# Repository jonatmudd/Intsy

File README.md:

# Intsy
32/64/128 channel bioamplifier system, now with accelerometer and on-board SD data logging capability for ambulatory applications! Photos of the original 32/64 channel device are below Also, check out the quick overview of the device internals and mechanical enclosure of the 128 channel ambulatory system in <a href =  "https://www.youtube.com/watch?v=RvYDtEdVOBU&feature=youtu.be">this video</a> (full credit to Riwaj Shrestha, Suyash Mathema, and Jeremy Wharton!).

Intsy is a validated, low-cost, open-source, wireless-enabled bioamplifier system.  The system can be configured for 32, 64, or 128 channel operation.  It has been validated for acquiring high-quality gastrointesinal slow wave and surface EMG electrical signals.  For more details, see our <a href =  "http://iopscience.iop.org/article/10.1088/1361-6579/aaad51">published peer-reviewed article in Physiological Measurement</a>. We have also regularly used Intsy to make <a href = "https://ieeexplore.ieee.org/abstract/document/8839813"> body surface recordings of colonic motilty patterns</a> using  conventiona wet (gel) as well as dry electrodes (see <a  href = "https://link.springer.com/article/10.1007/s10439-023-03137-w"> this journal article  </a>) 

Data can be streamed either in wired configuration over USB or wirelessly via bluetooth.  A LabView GUI allows for real-time visualization and saving to hard disk for off-line analysis.  Data rates of 32 chan x 110 Hz can be stably transmitted over bluetooth.  The USB wired configuration can achieve up to 2 kHz x 128 chan.  Matlab functions for converting binary Intsy data files into matlab format are provided.

The name Intsy comes from the two core components: Intan RHD2132 bioamplifier chip + Teensy 3.6 microcontroller.

Please see "Intsy_Setup_Guide.pdf" for detailed instructions on how to set up the 32/64 channel Intsy system. Assembly time is typically about 4 hrs.  Total cost is about $1500 for the 32 channel system,  $2400 for the 64 channel system, and $6000 for the 128 channel system (the dominant cost being the Intan RHD2132 amplifier boards).  That means  you can build your very own high-quality, low-cost, portable bioamplifier system in just a single afternoon!

All feedback and suggestions are warmly welcomed. 

Above: Intsy 128 channel electronics and mechanical enclosure (circa May 2020)

Above: Intsy hardware architecture and device (32/64 channel original module circa Dec 2017)

Above: Screenshot of Intsy Labview front end to visualize and stream signals in real time. The figure shows propagating gastric slow waves.

<p><font size="16"><b>Disclaimer</b></font></p>
The Intsy electronics module is not a medical device nor is it intended for medical diagnosis and provided to you "as is," and we make no express or implied warranties whatsoever with respect to its functionality, operability, or use, including, without limitation, any implied warranties, fitness for a particular purpose, or infringement. We expressly disclaim any liability whatsoever for any direct, indirect, consequential, incidental or special damages, including, without limitation, lost revenues, lost profits, losses resulting from business interruption or loss of data, regardless of the form of action or legal theory under which the liability may be asserted, even if advised of the possibility of such damages. This bioamplifier module does not fall within the scope of the European Union directives regarding electromagnetic compatibility, restricted substances (RoHS), recycling (WEEE), FCC, CE or UL, and therefore may not meet the technical requirements of these directives or other related directives

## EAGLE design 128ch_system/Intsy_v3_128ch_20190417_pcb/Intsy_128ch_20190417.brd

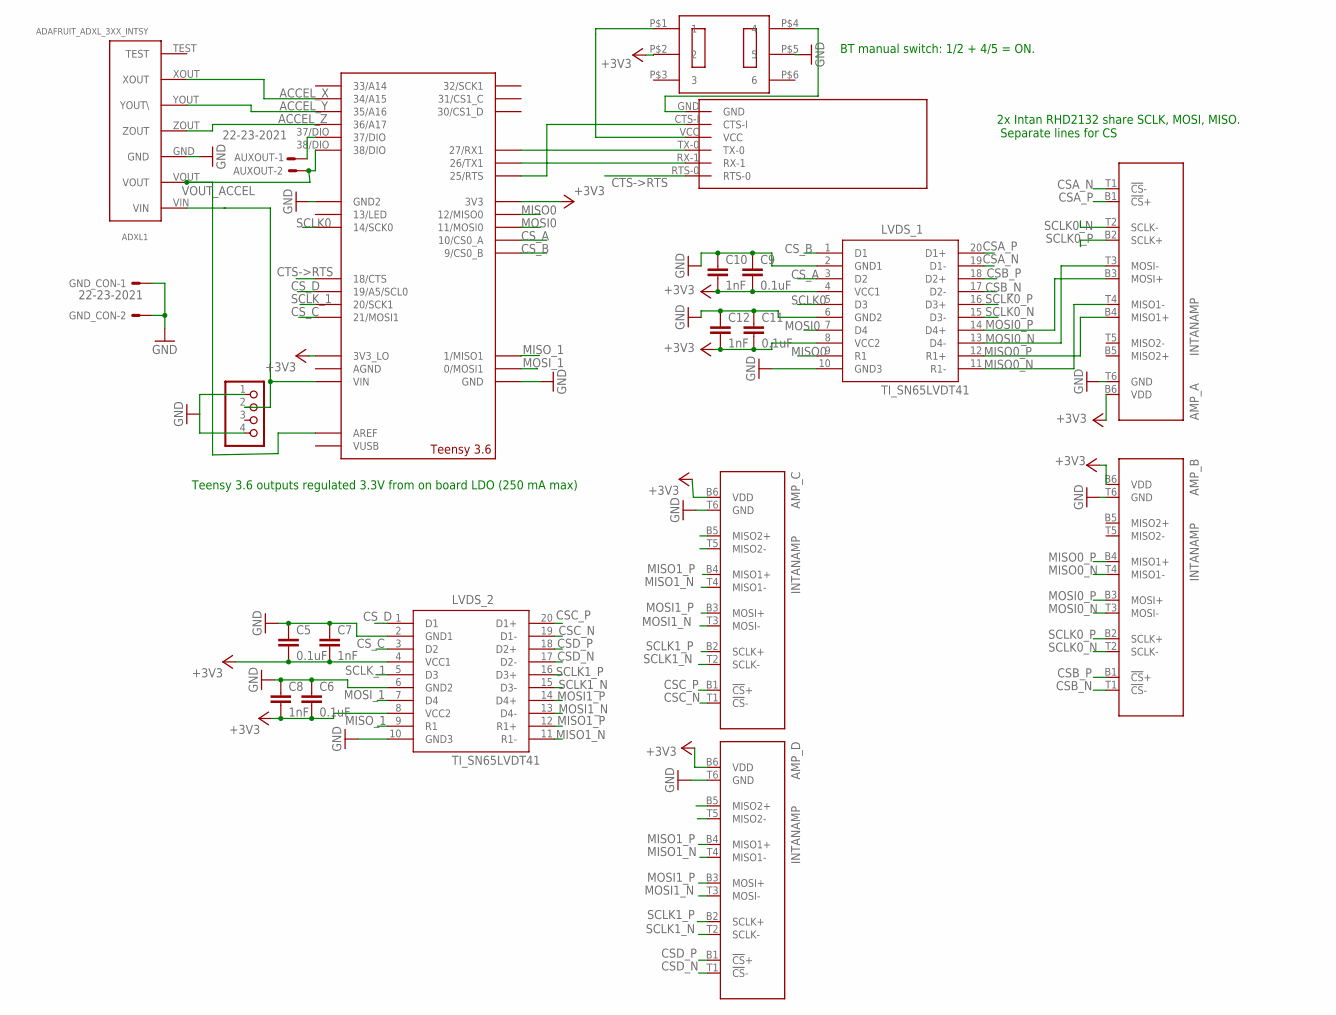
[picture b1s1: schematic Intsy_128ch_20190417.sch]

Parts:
ADXL1: ADAFRUIT_ADXL_3XX_INTSY; ADAFRUIT_ADXL_3XX
AMP_A: INTANAMP; AMPBOARD
AMP_B: INTANAMP; AMPBOARD
AMP_C: INTANAMP; AMPBOARD
AMP_D: INTANAMP; AMPBOARD
AUXOUT: 22-23-2021
C5, C6, C9, C11: 0.1uF; C2012
C7, C8, C10, C12: 1nF; C2012
DPDT_1: DPDT_1; SLIDE_SWITCH_DPDT_NIDEC
GND_CON: 22-23-2021
LVDS_1, LVDS_2: TI_SN65LVDT41; SN65LVDT41_TSSOP20
RN42: RN42
SW1: LiPoIn; PADS-4
U$2: TEENSY_3.5/3.6_SIMPLE

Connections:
+3V3: AMP_A.B6 (VDD), AMP_B.B6 (VDD), AMP_C.B6 (VDD), AMP_D.B6 (VDD), C5.2, C6.2, C7.2, C8.2, C9.2, C10.2, C11.2, C12.2, DPDT_1.P$2 (2), LVDS_1.4 (VCC1), LVDS_1.8 (VCC2), LVDS_2.4 (VCC1), LVDS_2.8 (VCC2), U$2.3V3, U$2.3V3_LO
ACCEL_X: ADXL1.XOUT, U$2.34/A15
ACCEL_Y: ADXL1.YOUT (YOUT\), U$2.35/A16
ACCEL_Z: ADXL1.ZOUT, U$2.36/A17
CSA_N: AMP_A.T1 (!CS!-), LVDS_1.19 (D1-)
CSA_P: AMP_A.B1 (!CS!+), LVDS_1.20 (D1+)
CSB_N: AMP_B.T1 (!CS!-), LVDS_1.17 (D2-)
CSB_P: AMP_B.B1 (!CS!+), LVDS_1.18 (D2+)
CSC_N: AMP_C.T1 (!CS!-), LVDS_2.19 (D1-)
CSC_P: AMP_C.B1 (!CS!+), LVDS_2.20 (D1+)
CSD_N: AMP_D.T1 (!CS!-), LVDS_2.17 (D2-)
CSD_P: AMP_D.B1 (!CS!+), LVDS_2.18 (D2+)
CS_A: LVDS_1.3 (D2), U$2.10/CS (10/CS0_A)
CS_B: LVDS_1.1 (D1), U$2.9/CS (9/CS0_B)
CS_C: LVDS_2.3 (D2), U$2.21/CS0/MOSI1 (21/MOSI1)
CS_D: LVDS_2.1 (D1), U$2.19/A5/SCL (19/A5/SCL0)
CTS->RTS: RN42.RTS-0, U$2.18/CTS
GND: ADXL1.GND, AMP_A.T6 (GND), AMP_B.T6 (GND), AMP_C.T6 (GND), AMP_D.T6 (GND), C5.1, C6.1, C7.1, C8.1, C9.1, C10.1, C11.1, C12.1, DPDT_1.P$5 (5), GND_CON.1, GND_CON.2, LVDS_1.2 (GND1), LVDS_1.6 (GND2), LVDS_1.10 (GND3), LVDS_2.2 (GND1), LVDS_2.6 (GND2), LVDS_2.10 (GND3), SW1.1, SW1.4, U$2.GND, U$2.GND2
MISO0: LVDS_1.9 (R1), U$2.12/MISO0
MISO0_N: AMP_A.T4 (MISO1-), AMP_B.T4 (MISO1-), LVDS_1.11 (R1-)
MISO0_P: AMP_A.B4 (MISO1+), AMP_B.B4 (MISO1+), LVDS_1.12 (R1+)
MISO1_N: AMP_C.T4 (MISO1-), AMP_D.T4 (MISO1-), LVDS_2.11 (R1-)
MISO1_P: AMP_C.B4 (MISO1+), AMP_D.B4 (MISO1+), LVDS_2.12 (R1+)
MISO_1: LVDS_2.9 (R1), U$2.1/MISO1
MOSI0: LVDS_1.7 (D4), U$2.11/MOSI0
MOSI0_N: AMP_A.T3 (MOSI-), AMP_B.T3 (MOSI-), LVDS_1.13 (D4-)
MOSI0_P: AMP_A.B3 (MOSI+), AMP_B.B3 (MOSI+), LVDS_1.14 (D4+)
MOSI1_N: AMP_C.T3 (MOSI-), AMP_D.T3 (MOSI-), LVDS_2.13 (D4-)
MOSI1_P: AMP_C.B3 (MOSI+), AMP_D.B3 (MOSI+), LVDS_2.14 (D4+)
MOSI_1: LVDS_2.7 (D4), U$2.0/MOSI1
unnamed: ADXL1.VIN, SW1.2, U$2.VIN
unnamed: AUXOUT.1, U$2.37/DIO
unnamed: DPDT_1.P$4 (4), RN42.GND
unnamed: RN42.TX-0, U$2.27/RX1
unnamed: RN42.RX-1, U$2.26/TX1
unnamed: RN42.CTS-I, U$2.25/RTS
unnamed: DPDT_1.P$1 (1), RN42.VCC
SCLK0: LVDS_1.5 (D3), U$2.14/SCK0
SCLK0_N: AMP_A.T2 (SCLK-), AMP_B.T2 (SCLK-), LVDS_1.15 (D3-)
SCLK0_P: AMP_A.B2 (SCLK+), AMP_B.B2 (SCLK+), LVDS_1.16 (D3+)
SCLK1_N: AMP_C.T2 (SCLK-), AMP_D.T2 (SCLK-), LVDS_2.15 (D3-)
SCLK1_P: AMP_C.B2 (SCLK+), AMP_D.B2 (SCLK+), LVDS_2.16 (D3+)
SCLK_1: LVDS_2.5 (D3), U$2.20/CS0/SCK1 (20/SCK1)
VOUT_ACCEL: ADXL1.VOUT, AUXOUT.2, U$2.38/DIO, U$2.AREF

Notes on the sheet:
2x Intan RHD2132 share SCLK, MOSI, MISO. Separate lines for CS
Teensy 3.6 outputs regulated 3.3V from on board LDO (250 mA max)
BT manual switch: 1/2 + 4/5 = ON.

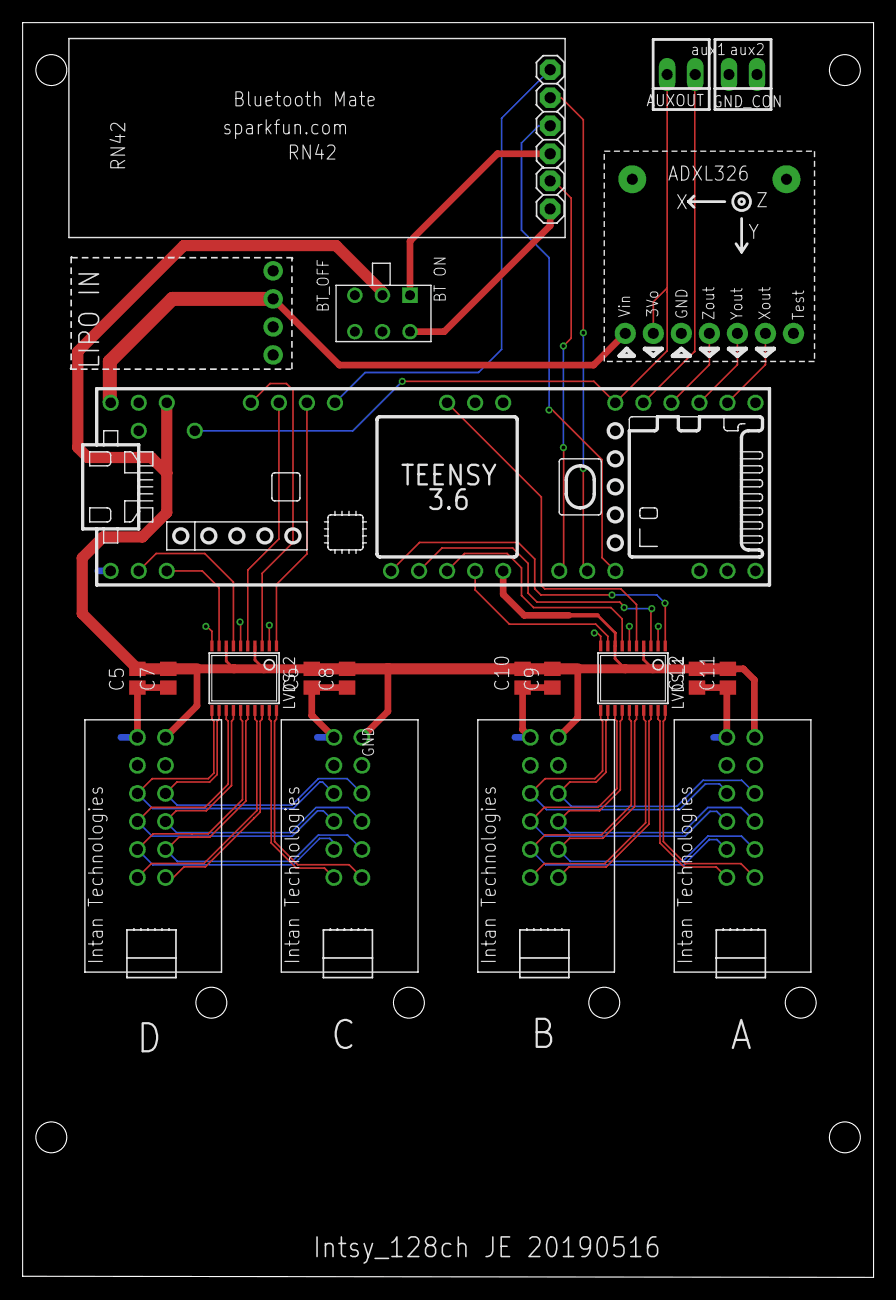
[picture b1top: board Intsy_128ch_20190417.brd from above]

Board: 2 copper layers, 77.1 x 113.7 mm, 21 parts (1 on the bottom side), 44 nets.

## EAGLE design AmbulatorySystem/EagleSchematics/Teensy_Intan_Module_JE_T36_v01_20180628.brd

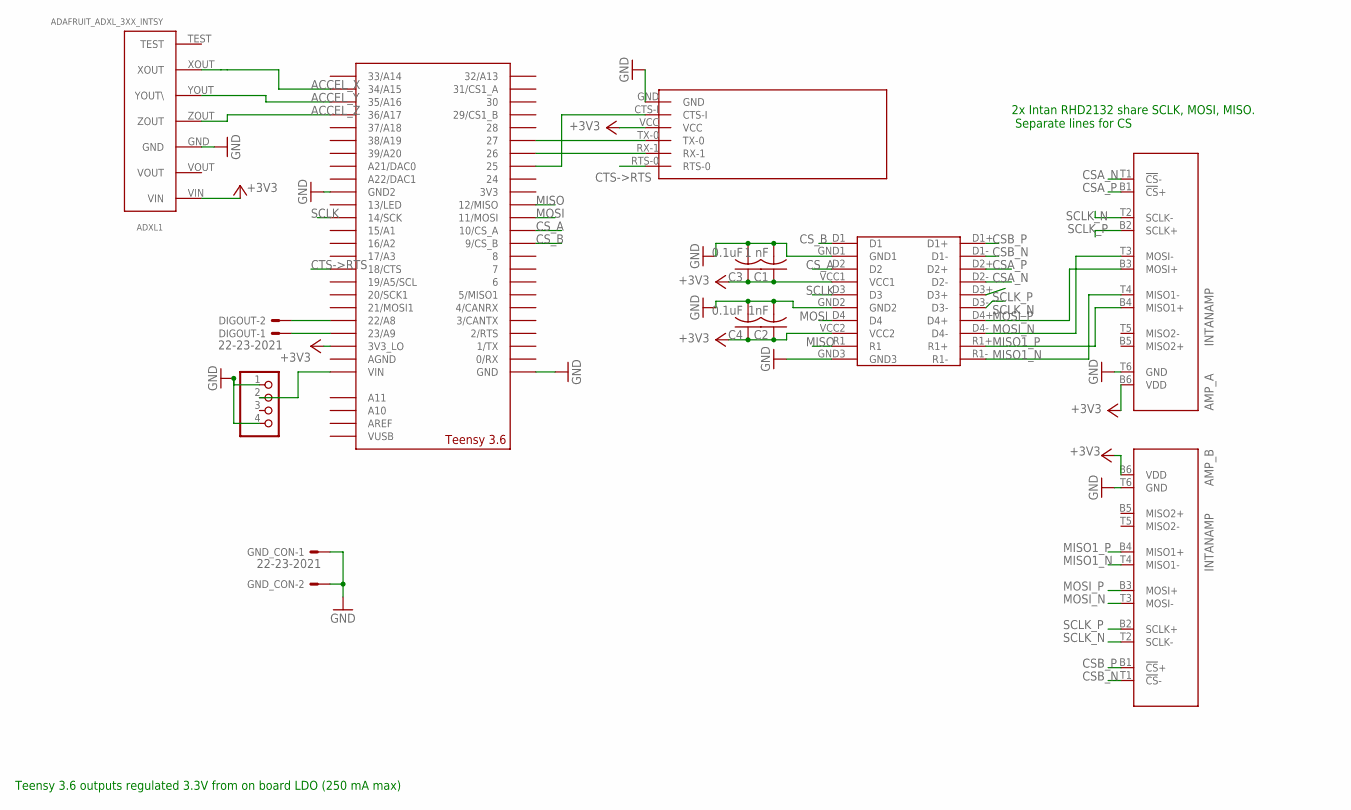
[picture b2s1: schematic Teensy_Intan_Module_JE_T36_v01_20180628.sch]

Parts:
ADXL1: ADAFRUIT_ADXL_3XX_INTSY; ADAFRUIT_ADXL_3XX
AMP_A: INTANAMP; AMPBOARD
AMP_B: INTANAMP; AMPBOARD
C1: 1 nF; C025-024X044
C2: 1nF; C025-024X044
C3, C4: 0.1uF; C025-024X044
DIGOUT: 22-23-2021
GND_CON: 22-23-2021
RN42: RN42
SW1: LiPoIn; PADS-4
U$1: SCHMARTBOARD20PIN
U$2: TEENSY_3.5/3.6_BASIC

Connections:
+3V3: ADXL1.VIN, AMP_A.B6 (VDD), AMP_B.B6 (VDD), C1.1, C2.1, C3.1, C4.1, RN42.VCC, U$1.VCC1, U$1.VCC2, U$2.3V3_LO
ACCEL_X: ADXL1.XOUT, U$2.34/A15
ACCEL_Y: ADXL1.YOUT (YOUT\), U$2.35/A16
ACCEL_Z: ADXL1.ZOUT, U$2.36/A17
CSA_N: AMP_A.T1 (!CS!-), U$1.D2-
CSA_P: AMP_A.B1 (!CS!+), U$1.D2+
CSB_N: AMP_B.T1 (!CS!-), U$1.D1-
CSB_P: AMP_B.B1 (!CS!+), U$1.D1+
CS_A: U$1.D2, U$2.10/CS (10/CS_A)
CS_B: U$1.D1, U$2.9/CS (9/CS_B)
CTS->RTS: RN42.RTS-0, U$2.18/A4/SDA (18/CTS)
GND: ADXL1.GND, AMP_A.T6 (GND), AMP_B.T6 (GND), C1.2, C2.2, C3.2, C4.2, GND_CON.1, GND_CON.2, RN42.GND, SW1.1, SW1.4, U$1.GND1, U$1.GND2, U$1.GND3, U$2.GND, U$2.GND2
MISO: U$1.R1, U$2.12/MISO
MISO1_N: AMP_A.T4 (MISO1-), AMP_B.T4 (MISO1-), U$1.R1-
MISO1_P: AMP_A.B4 (MISO1+), AMP_B.B4 (MISO1+), U$1.R1+
MOSI: U$1.D4, U$2.11/MOSI
MOSI_N: AMP_A.T3 (MOSI-), AMP_B.T3 (MOSI-), U$1.D4-
MOSI_P: AMP_A.B3 (MOSI+), AMP_B.B3 (MOSI+), U$1.D4+
unnamed: SW1.2, U$2.VIN
unnamed: DIGOUT.2, U$2.22/A8
unnamed: DIGOUT.1, U$2.23/A9
unnamed: RN42.TX-0, U$2.27
unnamed: RN42.RX-1, U$2.26
unnamed: RN42.CTS-I, U$2.25
SCLK: U$1.D3, U$2.14/A0 (14/SCK)
SCLK_N: AMP_A.T2 (SCLK-), AMP_B.T2 (SCLK-), U$1.D3-
SCLK_P: AMP_A.B2 (SCLK+), AMP_B.B2 (SCLK+), U$1.D3+

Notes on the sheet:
2x Intan RHD2132 share SCLK, MOSI, MISO. Separate lines for CS
Teensy 3.6 outputs regulated 3.3V from on board LDO (250 mA max)

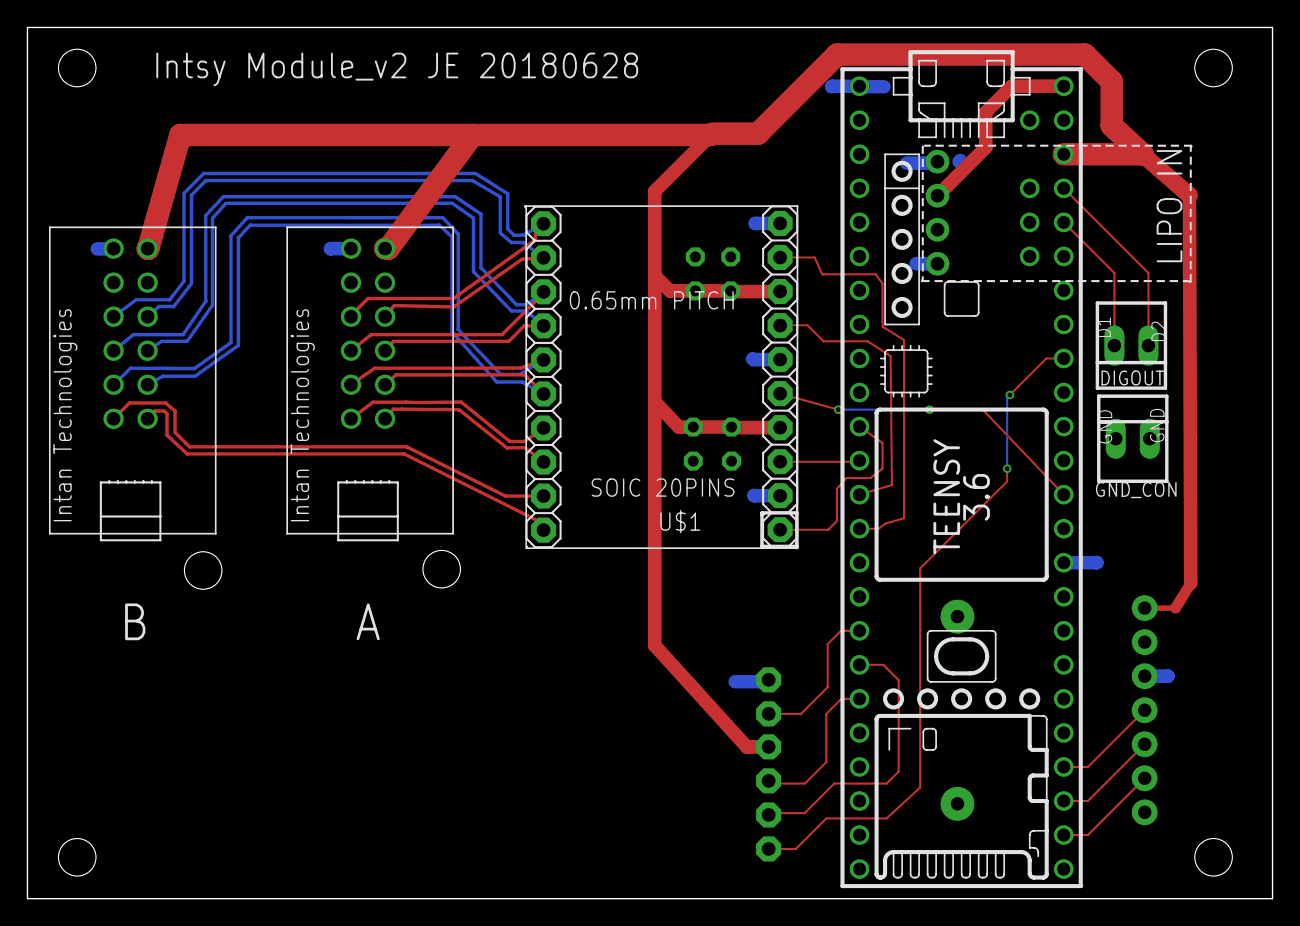
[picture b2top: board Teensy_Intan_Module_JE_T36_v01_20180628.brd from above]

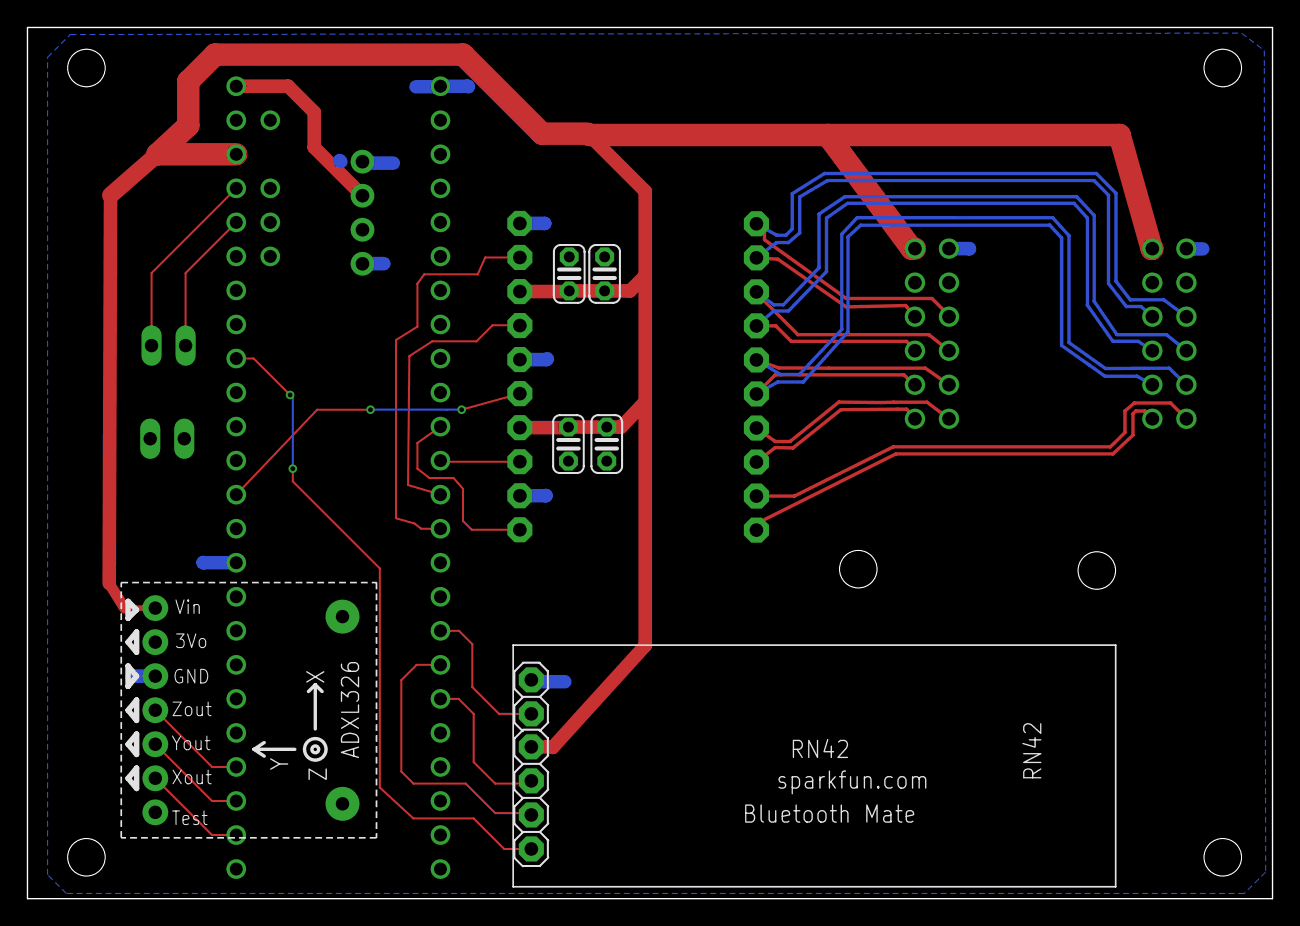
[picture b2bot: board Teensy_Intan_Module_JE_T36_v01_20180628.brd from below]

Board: 2 copper layers, 92.9 x 65.0 mm, 13 parts (6 on the bottom side), 27 nets.

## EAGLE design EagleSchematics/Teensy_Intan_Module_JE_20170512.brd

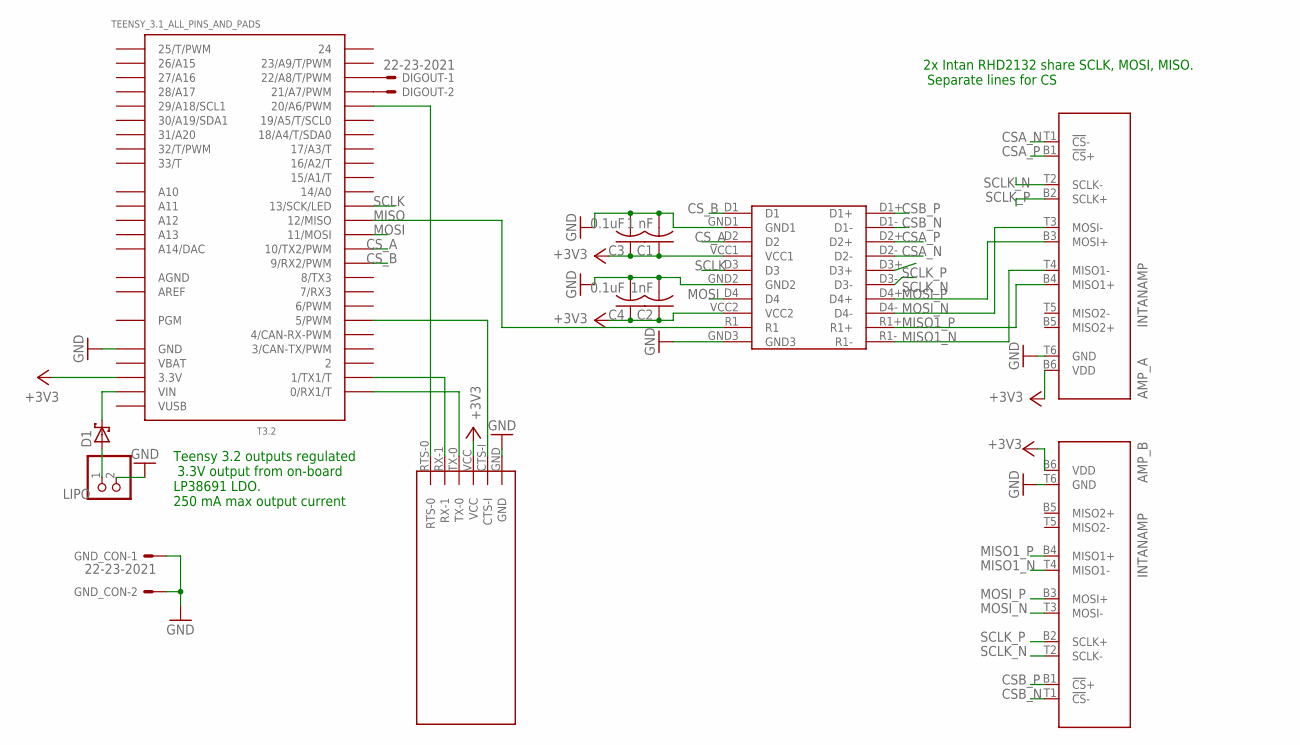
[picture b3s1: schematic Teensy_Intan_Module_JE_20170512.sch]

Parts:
AMP_A: INTANAMP; AMPBOARD
AMP_B: INTANAMP; AMPBOARD
C1: 1 nF; C025-024X044
C2: 1nF; C025-024X044
C3, C4: 0.1uF; C025-024X044
D1: SCHOTTKY-DIODEDO41-7; DO41-7
DIGOUT: 22-23-2021
GND_CON: 22-23-2021
LIPO: LIPO_BAT; JST-PH-2-THM
RN42: RN42
T3.2: TEENSY_3.1_ALL_PINS_AND_PADS; TEENSY_3.1_ALLPINS
U$1: SCHMARTBOARD20PIN

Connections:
+3V3: AMP_A.B6 (VDD), AMP_B.B6 (VDD), C1.1, C2.1, C3.1, C4.1, RN42.VCC, T3.2.3.3V, T3.2.3.3V1 (3.3V), T3.2.3.3V2 (3.3V), U$1.VCC1, U$1.VCC2
AGND: T3.2.AGND
AREF: T3.2.AREF
CSA_N: AMP_A.T1 (!CS!-), U$1.D2-
CSA_P: AMP_A.B1 (!CS!+), U$1.D2+
CSB_N: AMP_B.T1 (!CS!-), U$1.D1-
CSB_P: AMP_B.B1 (!CS!+), U$1.D1+
CS_A: T3.2.10 (10/TX2/PWM), U$1.D2
CS_B: T3.2.9 (9/RX2/PWM), U$1.D1
GND: AMP_A.T6 (GND), AMP_B.T6 (GND), C1.2, C2.2, C3.2, C4.2, GND_CON.1, GND_CON.2, LIPO.2 (1), RN42.GND, T3.2.GND, T3.2.GND1 (GND), T3.2.GND2 (GND), U$1.GND1, U$1.GND2, U$1.GND3
MISO: T3.2.12 (12/MISO), U$1.R1
MISO1_N: AMP_A.T4 (MISO1-), AMP_B.T4 (MISO1-), U$1.R1-
MISO1_P: AMP_A.B4 (MISO1+), AMP_B.B4 (MISO1+), U$1.R1+
MOSI: T3.2.11 (11/MOSI), U$1.D4
MOSI_N: AMP_A.T3 (MOSI-), AMP_B.T3 (MOSI-), U$1.D4-
MOSI_P: AMP_A.B3 (MOSI+), AMP_B.B3 (MOSI+), U$1.D4+
unnamed: D1.A, LIPO.1 (2)
unnamed: DIGOUT.1, T3.2.22/A8 (22/A8/T/PWM)
unnamed: DIGOUT.2, T3.2.21/A7 (21/A7/PWM)
unnamed: RN42.CTS-I, T3.2.5 (5/PWM)
unnamed: RN42.RTS-0, T3.2.20/A6 (20/A6/PWM)
RX-TN42: RN42.TX-0, T3.2.0 (0/RX1/T)
SCLK: T3.2.13 (13/SCK/LED), U$1.D3
SCLK_N: AMP_A.T2 (SCLK-), AMP_B.T2 (SCLK-), U$1.D3-
SCLK_P: AMP_A.B2 (SCLK+), AMP_B.B2 (SCLK+), U$1.D3+
TX-RN42: RN42.RX-1, T3.2.1 (1/TX1/T)
VBAT: T3.2.VBAT
VIN_LIPO: D1.C, T3.2.VIN
VUSB: T3.2.VUSB

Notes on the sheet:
2x Intan RHD2132 share SCLK, MOSI, MISO. Separate lines for CS
Teensy 3.2 outputs regulated 3.3V output from on-board LP38691 LDO. 250 mA max output current

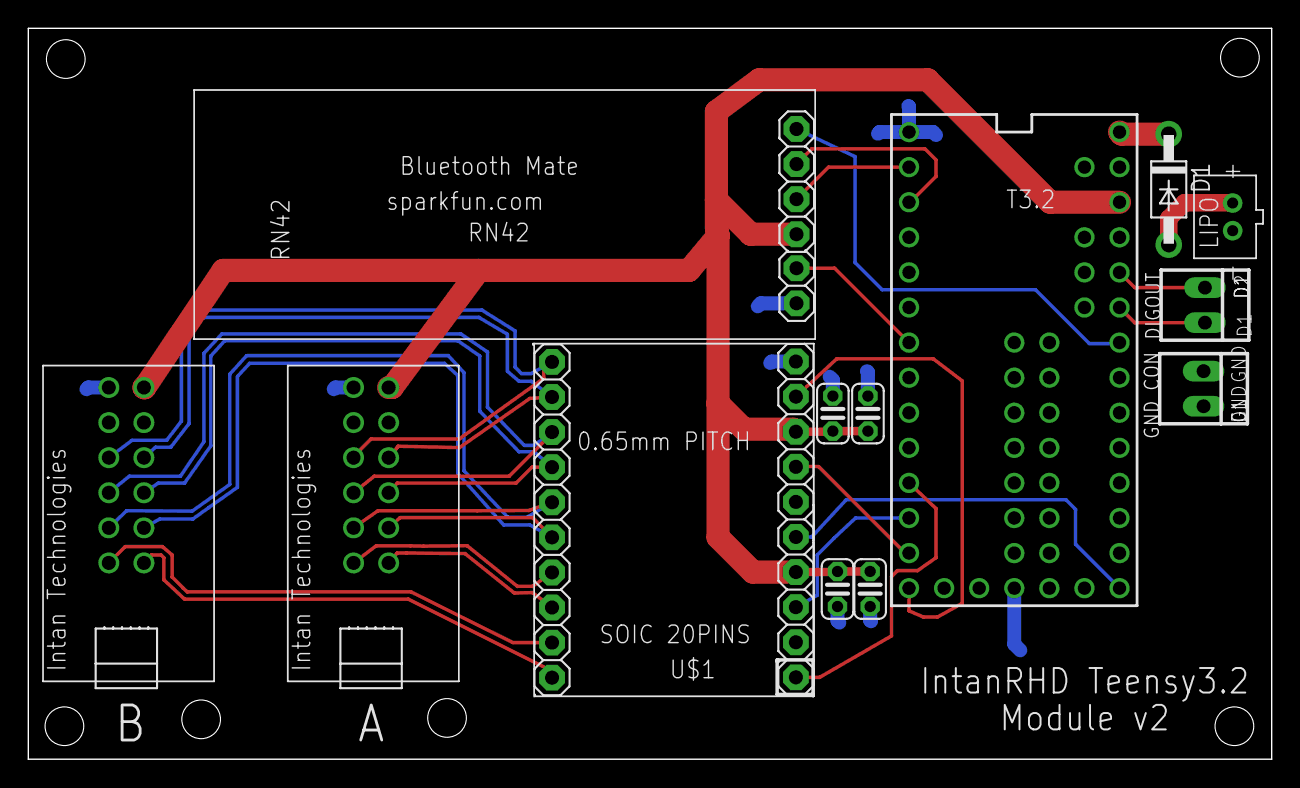
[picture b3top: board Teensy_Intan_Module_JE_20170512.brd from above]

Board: 2 copper layers, 90.0 x 52.9 mm, 13 parts (0 on the bottom side), 25 nets.

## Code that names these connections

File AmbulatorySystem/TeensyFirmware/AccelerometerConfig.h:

//accelerometer pins for analog reads
const int PIN_ACCEL_X = 34;
const int PIN_ACCEL_Y = 35;
const int PIN_ACCEL_Z = 36;
uint16_t accelX;
uint16_t accelY;
uint16_t accelZ;

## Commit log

2017-09-28 Add files via upload
    LV software for 32 chan system
2017-09-28 Add files via upload
    LV for 64 chan system
2017-09-28 Add files via upload
    loads .tsy files in matlab file format. one function each for 32 and 64 chan systems
2017-09-28 Add files via upload
    some helpful datasheets for developers
2017-09-28 Add files via upload
    overview of Intsy system
2017-10-01 Add files via upload
    add bill of materials. covers 32 and 64 chan
2017-10-03 Add files via upload
    screenshot of LabView interface
2017-11-08 Adding setup guide
    Instructions for assembly hardware module, powering the device, firmware uploading, and connecting to host PC wired or wirelessly
2018-02-13 Modified USB isolator
    Photo of modified Adafruit USB isolator + isolated DC-DC power supply for Intsy module. This module must be modified for compatibility with 3.3 V logic prior to using with Intsy system
2018-11-16 Add files via upload
    32/64-channel ambulatory module schematic and pcb lyaout. New module includes microSD card and ADXL3xx accelerometer
2018-12-17 Update README.md
    adding ambulatory system
2018-12-17 Update README.md
    ambulatory module updates
2018-12-17 Add files via upload
    ambulatory system PCB front/back
2018-12-17 Add files via upload
    gerbers for ambulatory module
2018-12-17 Create overview.md
    all design files, firmware and LV interface for ambulatory system with accelerometer and SD logging
2018-12-17 Create Firmware
2018-12-17 Add files via upload
    Teensy 3.6 firmware upload
2018-12-17 Create Overview.txt
    Labview files to interface to Intsy
2018-12-17 Create Overview.txt
    Eagle files and gerbers for board fab
2018-12-17 Update Firmware
2025-02-26 add 128 chan figure
2025-02-26 add BOM
2025-02-26 3d print mechanical enclosure files
2025-02-26 added pcb files
2025-02-26 add firmware
    main file is: Intan_128ch_20190708.ino
2025-02-26 Create labview folder
2025-02-26 remainder of lv files
    'other_nonIntan' folder probably not needed (lost to history at the moment)
2025-02-26 Create readme_matlab
2025-02-26 Create readme_firmware
2025-02-26 Update readme_firmware
2025-02-26 Create readme_pcb
2025-02-26 Create readme_labview

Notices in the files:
parts and their libraries:
SparkFun-Aesthetics: Licensing: Creative Commons ShareAlike 4.0 International - https://creativecommons.org/licenses/by-sa/4.0
